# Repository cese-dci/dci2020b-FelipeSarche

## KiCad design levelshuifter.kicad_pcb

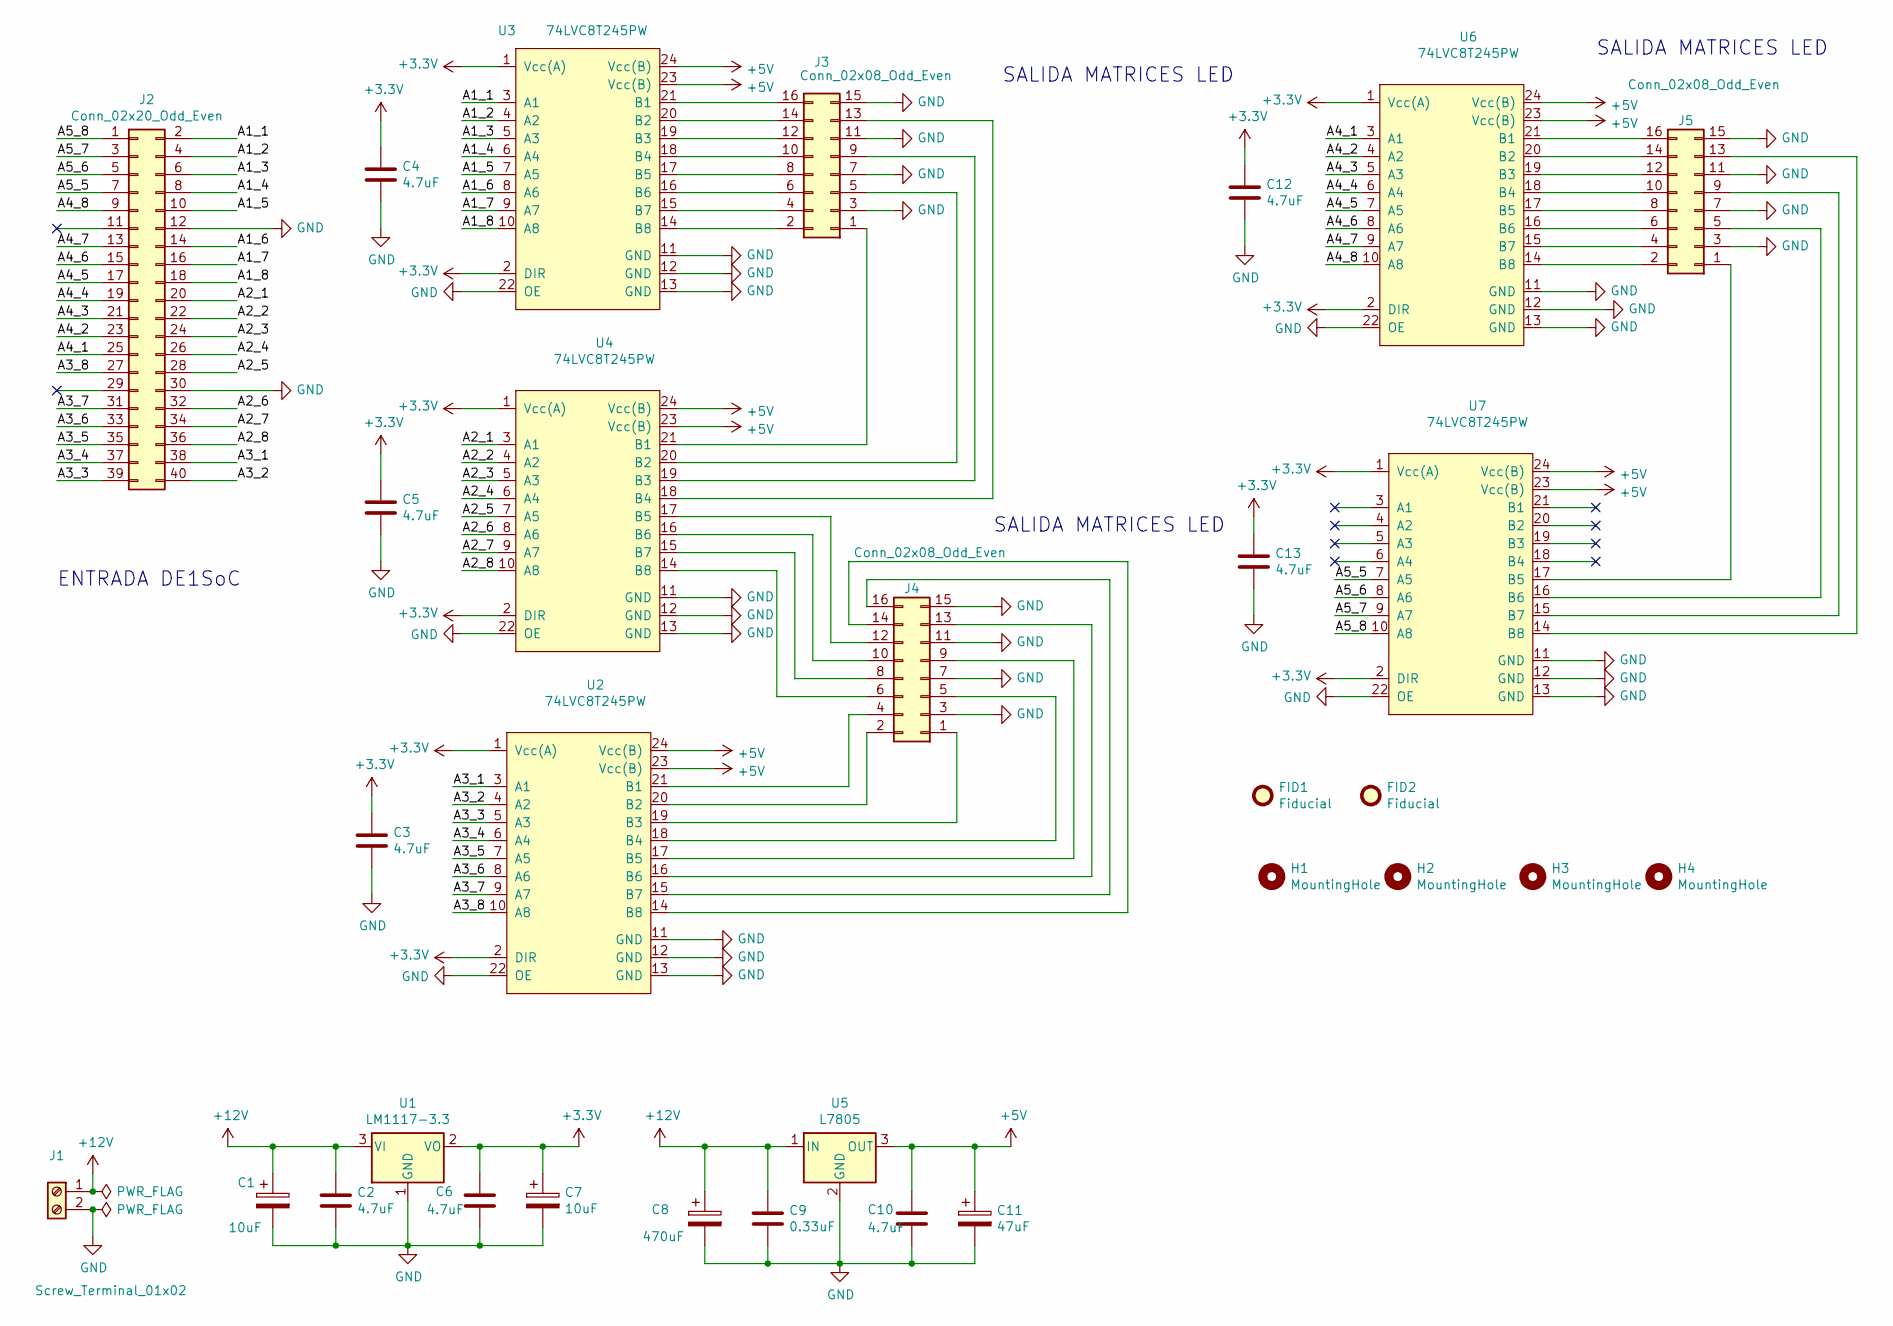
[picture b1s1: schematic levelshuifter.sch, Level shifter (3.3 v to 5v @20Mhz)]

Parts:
C1, C7: 10uF; C_Radial_D5.0mm_H7.0mm_P2.00mm
C2, C3, C4, C5, C6, C10, C12, C13: 4.7uF; C_0805_2012Metric
C8: 470uF; C_Radial_D10.0mm_H20.0mm_P5.00mm
C9: 0.33uF; C_0805_2012Metric
C11: 47uF; C_Radial_D6.3mm_H11.0mm_P2.50mm
FID1, FID2: Fiducial; Fiducial_1mm_Mask2mm
H1, H2, H3, H4: MountingHole; MountingHole_3mm
J1: Screw_Terminal_01x02; TerminalBlock_bornier-2_P5.08mm
J2: Conn_02x20_Odd_Even; PinHeader_2x20_P2.54mm_Vertical
J3, J4, J5: Conn_02x08_Odd_Even; PinHeader_2x08_P2.54mm_Vertical
U1: LM1117-3.3; SOT-223
U2, U3, U4, U6, U7: 74LVC8T245PW; TSSOP-24_4.4x7.8mm_P0.65mm
U5: L7805; TO-263-3_TabPin2

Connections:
+3V3: C3.1, C4.1, C5.1, C6.1, C7.1, C12.1, C13.1, U1.2 (VO), U2.1 (Vcc(A)), U2.2 (DIR), U3.1 (Vcc(A)), U3.2 (DIR), U4.1 (Vcc(A)), U4.2 (DIR), U6.1 (Vcc(A)), U6.2 (DIR), U7.1 (Vcc(A)), U7.2 (DIR)
+5V: C10.1, C11.1, U2.23 (Vcc(B)), U2.24 (Vcc(B)), U3.23 (Vcc(B)), U3.24 (Vcc(B)), U4.23 (Vcc(B)), U4.24 (Vcc(B)), U5.3 (OUT), U6.23 (Vcc(B)), U6.24 (Vcc(B)), U7.23 (Vcc(B)), U7.24 (Vcc(B))
+12V: C1.1, C2.1, C8.1, C9.1, J1.1, U1.3 (VI), U5.1 (IN)
/A1_1: J2.2, U3.3 (A1)
/A1_2: J2.4, U3.4 (A2)
/A1_3: J2.6, U3.5 (A3)
/A1_4: J2.8, U3.6 (A4)
/A1_5: J2.10, U3.7 (A5)
/A1_6: J2.14, U3.8 (A6)
/A1_7: J2.16, U3.9 (A7)
/A1_8: J2.18, U3.10 (A8)
/A2_1: J2.20, U4.3 (A1)
/A2_2: J2.22, U4.4 (A2)
/A2_3: J2.24, U4.5 (A3)
/A2_4: J2.26, U4.6 (A4)
/A2_5: J2.28, U4.7 (A5)
/A2_6: J2.32, U4.8 (A6)
/A2_7: J2.34, U4.9 (A7)
/A2_8: J2.36, U4.10 (A8)
/A3_1: J2.38, U2.3 (A1)
/A3_2: J2.40, U2.4 (A2)
/A3_3: J2.39, U2.5 (A3)
/A3_4: J2.37, U2.6 (A4)
/A3_5: J2.35, U2.7 (A5)
/A3_6: J2.33, U2.8 (A6)
/A3_7: J2.31, U2.9 (A7)
/A3_8: J2.27, U2.10 (A8)
/A4_1: J2.25, U6.3 (A1)
/A4_2: J2.23, U6.4 (A2)
/A4_3: J2.21, U6.5 (A3)
/A4_4: J2.19, U6.6 (A4)
/A4_5: J2.17, U6.7 (A5)
/A4_6: J2.15, U6.8 (A6)
/A4_7: J2.13, U6.9 (A7)
/A4_8: J2.9, U6.10 (A8)
/A5_5: J2.7, U7.7 (A5)
/A5_6: J2.5, U7.8 (A6)
/A5_7: J2.3, U7.9 (A7)
/A5_8: J2.1, U7.10 (A8)
GND: C1.2, C2.2, C3.2, C4.2, C5.2, C6.2, C7.2, C8.2, C9.2, C10.2, C11.2, C12.2, C13.2, J1.2, J2.12, J2.30, J3.3, J3.7, J3.11, J3.15, J4.3, J4.7, J4.11, J4.15, J5.3, J5.7, J5.11, J5.15, U1.1 (GND), U2.11 (GND), U2.12 (GND), U2.13 (GND), U2.22 (OE), U3.11 (GND), U3.12 (GND), U3.13 (GND), U3.22 (OE), U4.11 (GND), U4.12 (GND), U4.13 (GND), U4.22 (OE), U5.2 (GND), U6.11 (GND), U6.12 (GND), U6.13 (GND), U6.22 (OE), U7.11 (GND), U7.12 (GND), U7.13 (GND), U7.22 (OE)
unnamed: J3.1, U4.21 (B1)
unnamed: J3.2, U3.14 (B8)
unnamed: J3.4, U3.15 (B7)
unnamed: J3.5, U4.20 (B2)
unnamed: J3.6, U3.16 (B6)
unnamed: J3.8, U3.17 (B5)
unnamed: J3.9, U4.19 (B3)
unnamed: J3.10, U3.18 (B4)
unnamed: J3.12, U3.19 (B3)
unnamed: J3.13, U4.18 (B4)
unnamed: J3.14, U3.20 (B2)
unnamed: J3.16, U3.21 (B1)
unnamed: J4.1, U2.19 (B3)
unnamed: J4.2, U2.20 (B2)
unnamed: J4.4, U2.21 (B1)
unnamed: J4.5, U2.18 (B4)
unnamed: J4.6, U4.14 (B8)
unnamed: J4.8, U4.15 (B7)
unnamed: J4.9, U2.17 (B5)
unnamed: J4.10, U4.16 (B6)
unnamed: J4.12, U4.17 (B5)
unnamed: J4.13, U2.16 (B6)
unnamed: J4.14, U2.14 (B8)
unnamed: J4.16, U2.15 (B7)
unnamed: J5.1, U7.17 (B5)
unnamed: J5.2, U6.14 (B8)
unnamed: J5.4, U6.15 (B7)
unnamed: J5.5, U7.16 (B6)
unnamed: J5.6, U6.16 (B6)
unnamed: J5.8, U6.17 (B5)
unnamed: J5.9, U7.15 (B7)
unnamed: J5.10, U6.18 (B4)
unnamed: J5.12, U6.19 (B3)
unnamed: J5.13, U7.14 (B8)
unnamed: J5.14, U6.20 (B2)
unnamed: J5.16, U6.21 (B1)

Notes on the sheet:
ENTRADA DE1SoC
SALIDA MATRICES LED

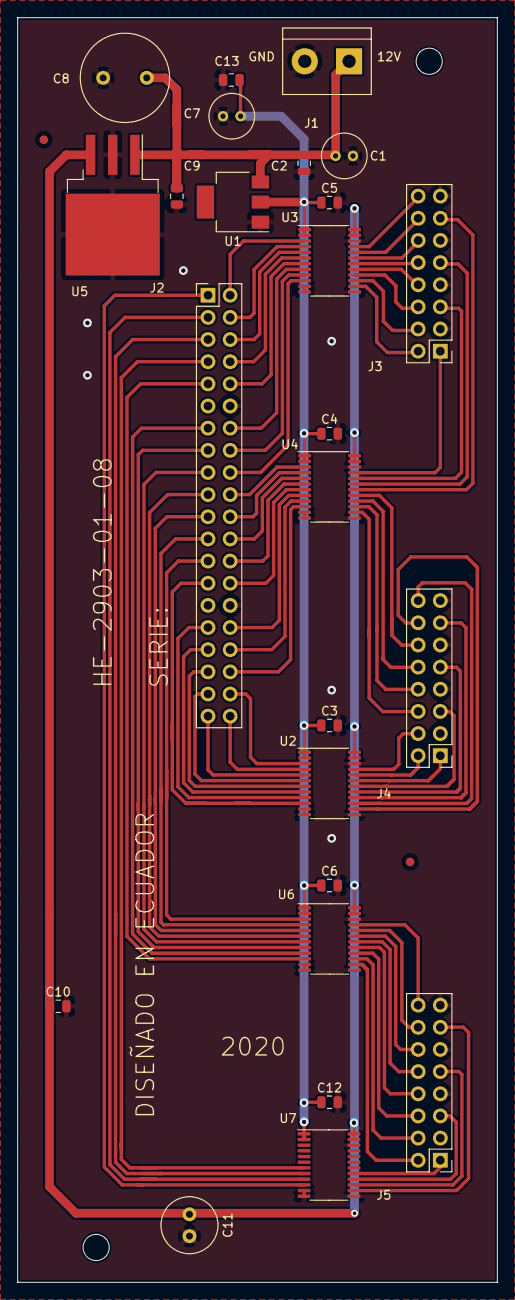
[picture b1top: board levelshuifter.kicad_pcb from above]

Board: 2 copper layers, 55.0 x 145.0 mm, 29 parts (0 on the bottom side), 76 nets.

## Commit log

2020-10-05 cambio de membrete
2020-10-05 datasheets agregados
2020-10-15 segundos cambios
2020-10-15 documentacion agregada
2020-10-15 agrego modelos 3d
2020-10-16 anotaciones solucionadas
2020-10-16 fixed 3d
2020-10-29 sugerencias agregadas parcialmente
2020-11-02 cambios 2
2020-11-02 cambios docu
2020-11-02 NOTAS
2020-11-02 nota de ultima

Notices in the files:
levelshuifter.kicad_pcb:
Bajo licencia Creative Commons Attribution Share - Alike 4.0
levelshuifter.sch:
https://creativecommons.org/licenses/by-sa/4.0
